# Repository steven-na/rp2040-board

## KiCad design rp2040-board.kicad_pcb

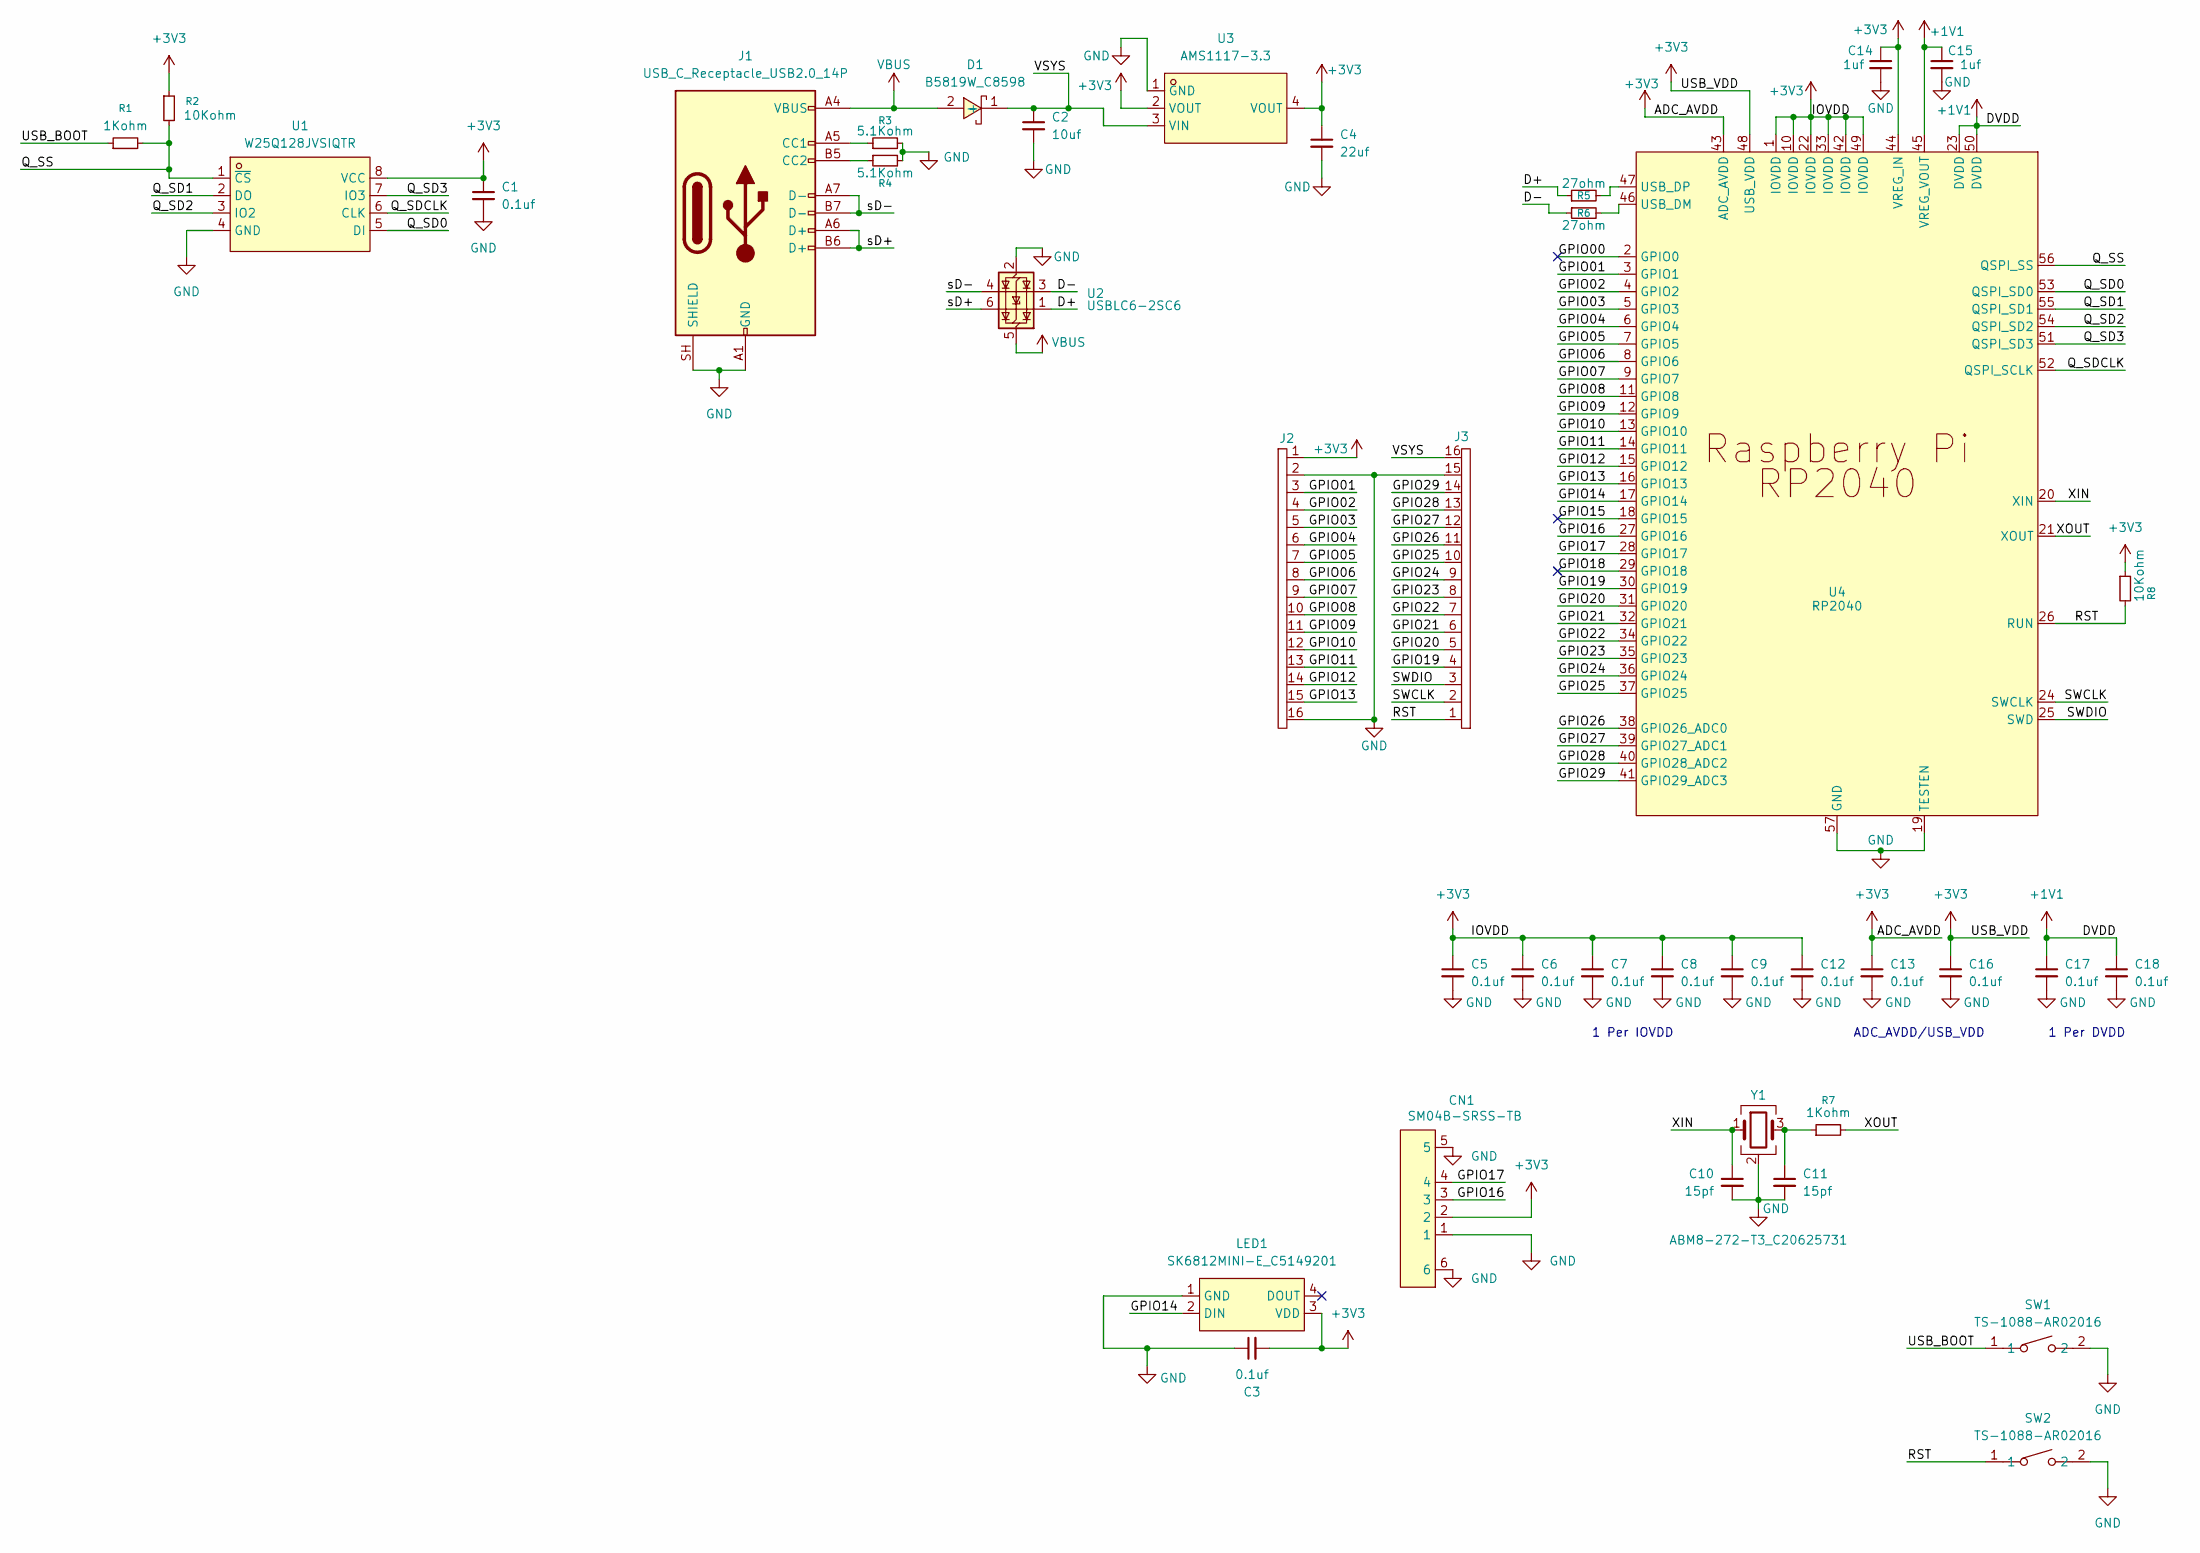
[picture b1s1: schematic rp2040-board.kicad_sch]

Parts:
C1, C3, C5, C6, C7, C8, C9, C12, C13, C16, C17, C18: 0.1uf; C_0402_1005Metric; LCSC Part C1525
C2: 10uf; C_0402_1005Metric; LCSC Part C15525
C4: 22uf; C_0603_1608Metric; LCSC Part C59461
C10, C11: 15pf; C_0402_1005Metric; LCSC Part C1548
C14, C15: 1uf; C_0402_1005Metric; LCSC Part C52923
CN1: SM04B-SRSS-TB; CONN-SMD_4P-P1.00_SM04B-SRSS-TB-LF-SN; MPN SM04B-SRSS-TB(LF)(SN); LCSC Part C160404
D1: B5819W_C8598; SOD-123_L2.7-W1.6-LS3.7-RD-1; MPN B5819W SL; LCSC Part C8598
J1: USB_C_Receptacle_USB2.0_14P; USB_C_Receptacle_HRO_TYPE-C-31-M-12_WITH_3D_MODEL; LCSC Part C165948
J2, J3: 2.0mm_16x1_castellated
LED1: SK6812MINI-E_C5149201; LED-SMD_4P-L3.2-W2.8-LS5.9_SK6812MINI-E; MPN SK6812MINI-E; LCSC Part C5149201
R1, R7: 1Kohm; R_0402_1005Metric; LCSC Part C11702
R2, R8: 10Kohm; R_0402_1005Metric; LCSC Part C60489
R3, R4: 5.1Kohm; R_0805_2012Metric; LCSC Part C27834
R5, R6: 27ohm; R_0603_1608Metric; LCSC Part C25190
SW1, SW2: TS-1088-AR02016; SW-SMD_L3.9-W3.0-P4.45; MPN TS-1088-AR02016; LCSC Part C720477
U1: W25Q128JVSIQTR; SOIC-8_L5.3-W5.3-P1.27-LS8.0-BL; MPN W25Q128JVSIQ; LCSC Part C97521
U2: USBLC6-2SC6; SOT-23-6; LCSC Part C7519
U3: AMS1117-3.3; SOT-223-3_L6.5-W3.4-P2.30-LS7.0-BR; MPN AMS1117-3.3; LCSC Part C6186
U4: RP2040; LQFN-56_L7.0-W7.0-P0.4-EP; MPN RP2040; LCSC Part C2040
Y1: ABM8-272-T3_C20625731; CRYSTAL-SMD_4P-L3.2-W2.5-BL; LCSC Part C20625731

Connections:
+1V1: C15.1, C17.1, C18.1, U4.23 (DVDD), U4.45 (VREG_VOUT), U4.50 (DVDD)
+3V3: C1.1, C3.2, C4.1, C5.1, C6.1, C7.1, C8.1, C9.1, C12.1, C13.1, C14.1, C16.1, CN1.2, J2.1, LED1.3 (VDD), R2.1, R8.1, U1.8 (VCC), U3.2 (VOUT), U3.4 (VOUT), U4.1 (IOVDD), U4.10 (IOVDD), U4.22 (IOVDD), U4.33 (IOVDD), U4.42 (IOVDD), U4.43 (ADC_AVDD), U4.44 (VREG_IN), U4.48 (USB_VDD), U4.49 (IOVDD)
/D+: R5.1, U2.1 (I/O1)
/D-: R6.1, U2.3 (I/O2)
/GPIO00: U4.2 (GPIO0)
/GPIO01: J2.3, U4.3 (GPIO1)
/GPIO02: J2.4, U4.4 (GPIO2)
/GPIO03: J2.5, U4.5 (GPIO3)
/GPIO04: J2.6, U4.6 (GPIO4)
/GPIO05: J2.7, U4.7 (GPIO5)
/GPIO06: J2.8, U4.8 (GPIO6)
/GPIO07: J2.9, U4.9 (GPIO7)
/GPIO08: J2.10, U4.11 (GPIO8)
/GPIO09: J2.11, U4.12 (GPIO9)
/GPIO10: J2.12, U4.13 (GPIO10)
/GPIO11: J2.13, U4.14 (GPIO11)
/GPIO12: J2.14, U4.15 (GPIO12)
/GPIO13: J2.15, U4.16 (GPIO13)
/GPIO14: LED1.2 (DIN), U4.17 (GPIO14)
/GPIO15: U4.18 (GPIO15)
/GPIO16: CN1.3, U4.27 (GPIO16)
/GPIO17: CN1.4, U4.28 (GPIO17)
/GPIO18: U4.29 (GPIO18)
/GPIO19: J3.4, U4.30 (GPIO19)
/GPIO20: J3.5, U4.31 (GPIO20)
/GPIO21: J3.6, U4.32 (GPIO21)
/GPIO22: J3.7, U4.34 (GPIO22)
/GPIO23: J3.8, U4.35 (GPIO23)
/GPIO24: J3.9, U4.36 (GPIO24)
/GPIO25: J3.10, U4.37 (GPIO25)
/GPIO26: J3.11, U4.38 (GPIO26_ADC0)
/GPIO27: J3.12, U4.39 (GPIO27_ADC1)
/GPIO28: J3.13, U4.40 (GPIO28_ADC2)
/GPIO29: J3.14, U4.41 (GPIO29_ADC3)
/Q_SD0: U1.5 (DI), U4.53 (QSPI_SD0)
/Q_SD1: U1.2 (DO), U4.55 (QSPI_SD1)
/Q_SD2: U1.3 (IO2), U4.54 (QSPI_SD2)
/Q_SD3: U1.7 (IO3), U4.51 (QSPI_SD3)
/Q_SDCLK: U1.6 (CLK), U4.52 (QSPI_SCLK)
/Q_SS: R1.2, R2.2, U1.1 (~CS), U4.56 (QSPI_SS)
/RST: J3.1, R8.2, SW2.1, U4.26 (RUN)
/SWCLK: J3.2, U4.24 (SWCLK)
/SWDIO: J3.3, U4.25 (SWD)
/USB_BOOT: R1.1, SW1.1
/VSYS: C2.1, D1.1 (-), J3.16, U3.3 (VIN)
/XIN: C10.1, U4.20 (XIN), Y1.1
/XOUT: R7.2, U4.21 (XOUT)
/sD+: J1.A6 (D+), J1.B6 (D+), U2.6 (I/O1)
/sD-: J1.A7 (D-), J1.B7 (D-), U2.4 (I/O2)
GND: C1.2, C2.2, C3.1, C4.2, C5.2, C6.2, C7.2, C8.2, C9.2, C10.2, C11.2, C12.2, C13.2, C14.2, C15.2, C16.2, C17.2, C18.2, CN1.1, CN1.5, CN1.6, J1.A1 (GND), J1.A12 (GND), J1.B1 (GND), J1.B12 (GND), J1.SH (SHIELD), J2.2, J2.16, J3.15, LED1.1 (GND), R3.2, R4.2, SW1.2, SW2.2, U1.4 (GND), U2.2 (GND), U3.1 (GND), U4.19 (TESTEN), U4.57 (GND), Y1.2 (G), Y1.4 (G)
unnamed: C11.1, R7.1, Y1.3
unnamed: J1.A5 (CC1), R3.1
unnamed: J1.B5 (CC2), R4.1
unnamed: R6.2, U4.46 (USB_DM)
unnamed: R5.2, U4.47 (USB_DP)
VBUS: D1.2 (+), J1.A4 (VBUS), J1.A9 (VBUS), J1.B4 (VBUS), J1.B9 (VBUS), U2.5 (VBUS)

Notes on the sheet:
1 Per DVDD
1 Per IOVDD
ADC_AVDD/USB_VDD

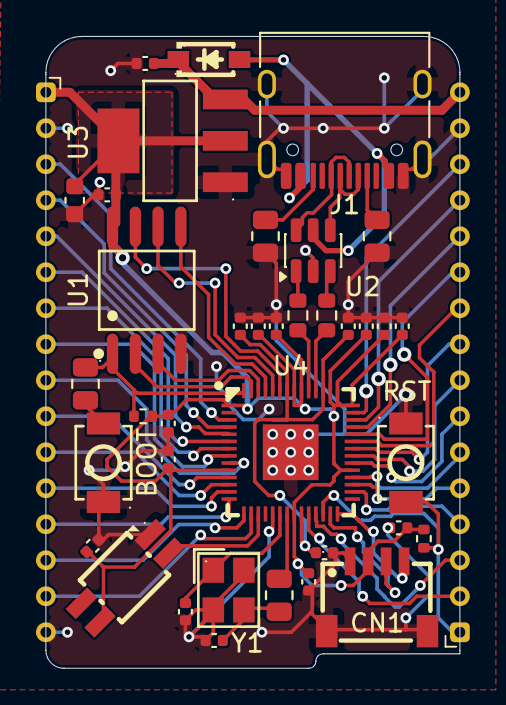
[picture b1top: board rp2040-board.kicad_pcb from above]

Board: 2 copper layers, 23.0 x 35.1 mm, 39 parts (0 on the bottom side), 53 nets.
